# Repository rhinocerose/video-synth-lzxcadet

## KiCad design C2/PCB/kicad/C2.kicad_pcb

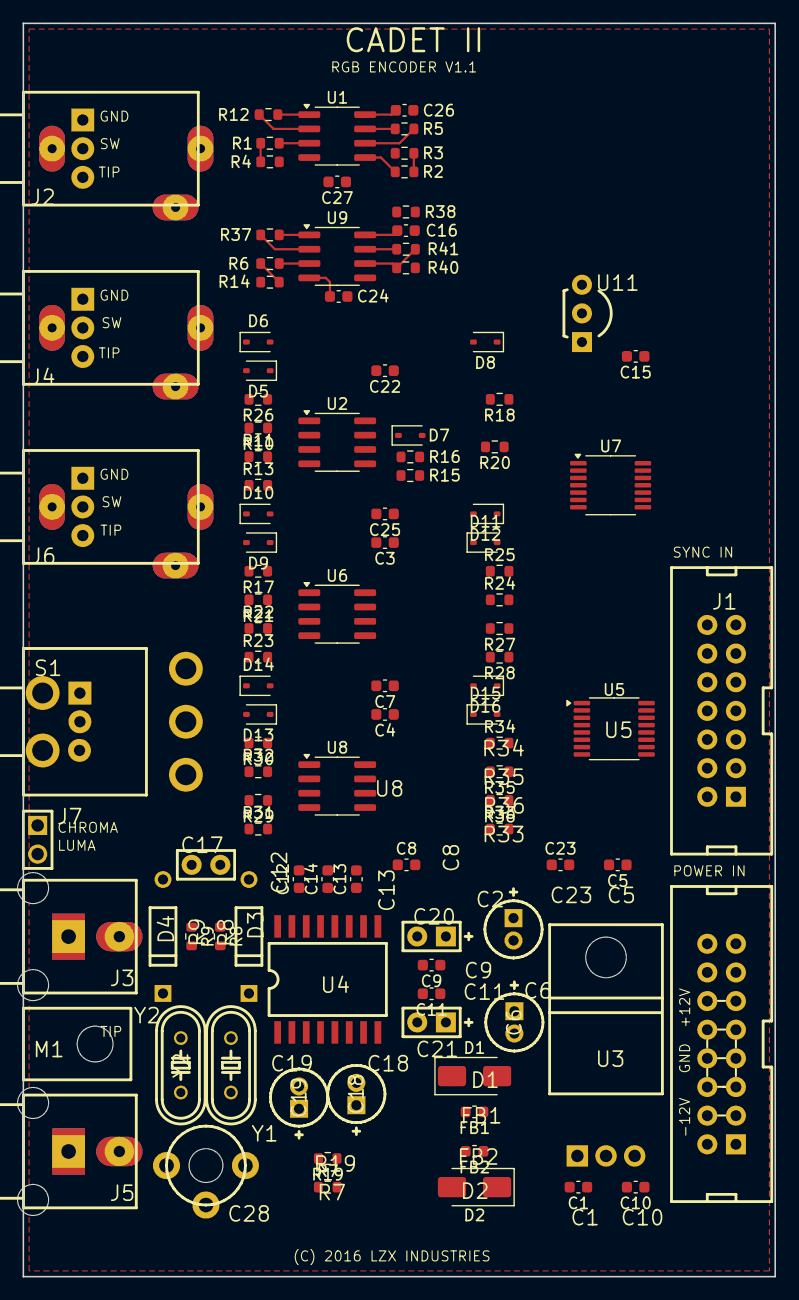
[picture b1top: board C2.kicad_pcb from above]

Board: 2 copper layers, 66.7 x 111.1 mm, 108 parts (0 on the bottom side), 77 nets.

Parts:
C1: 330n; C_0603_1608Metric
C2, C6: 10u 25V; CAPPR-2_5.08
C3, C4, C5, C7, C8, C10, C12, C13, C14, C15, C16, C22, C23, C24, C25, C26, C27: 100n; C_0603_1608Metric
C9, C11: 1u; C_0603_1608Metric
C17: DNP; CAP-2.54_6.6x3_C17
C18, C19: 220uF 6.3V; CAPPR-2_5.08
C20: 10u Tantalum; PCAP-2.54_6.6x3
C21: 10u Tantalum; PCAP-2.54_6.6x3_C21
C28: DNP; GYA22000
D1, D2: 1N4001; D_SMA
D3, D4: 1N4148; DO-35
D5, D6, D7, D8, D9, D10, D11, D12, D13, D14, D15, D16: 1N5711; D_SOD-323
FB1, FB2: 68R; L_0603_1608Metric
J1: LZXSYNC14; IDC14M
J2, J4, J6: 3.5MM_JACK; PJ302M
J3, J5: RCJ-04X
J7: 1X2 PIN HEADER; HDR-2x1T_2.54x2.54_3x5
J9: 2X8_PIN_HEADER; IDC16M
M1: KEYSTONE621
R1, R2, R6: 499R; R_0603_1608Metric
R3, R4, R14: 100K; R_0603_1608Metric
R5, R10, R11, R12, R15, R16, R17, R18, R20, R21, R22, R24, R25, R26, R27, R28, R29, R30, R31, R33, R34, R35, R36, R37, R41: 1K; R_0603_1608Metric
R7, R19: 75R; R_0603_1608Metric
R8, R9: 10K; R_0603_1608Metric
R13, R23, R32: 1.4K; R_0603_1608Metric
R38: 4.99K; R_0603_1608Metric
R40: 3.48K; R_0603_1608Metric
S1: 10TF230-DIY
U1, U2, U6, U8, U9: LM6172; SOIC-8_3.9x4.9mm_P1.27mm
U3: 7805; TO-220H
U4: AD724; SOIC-16_300mil
U5: CD4053; TSSOP-16_4.4x5mm_P0.65mm
U7: 74HC14; TSSOP-14_4.4x5mm_P0.65mm
U11: TL431; TO-92-100R
Y1: 3.58MHz; HC-49U
Y2: 4.43MHz; HC-49U

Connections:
+5V: C5.1, C9.1, C10.1, C11.1, C15.1, C20.1, C21.1, S1.3 (C2), S1.3B (C2), U3.3 (OUTPUT), U4.4, U4.5, U4.14, U4.15, U5.16 (VCC), U7.14 (VCC)
+12V: C1.1, C2.1 (PLUS), C3.1, C4.1, C16.1, C22.1, C26.1, FB1.2, R38.2 (B), U1.8 (V+), U3.1 (INPUT), U6.8 (V+), U8.8 (V+), U9.8 (V+)
-12V: C6.2 (MINUS), C7.2, C8.2, C23.2, C24.2, C25.2, C27.2, FB2.2, U1.4 (V-), U2.4 (V-), U5.7 (VEE), U6.4 (V-), U8.4 (V-), U9.4 (V-)
/Schematic1/2/CLIP_REF: R11.1 (A), R18.1 (A), R22.1 (A), R27.1 (A), R31.1 (A), R35.1 (A), R41.2 (B), U9.7 (OUT)
/Schematic2/2/BLANKING: U5.9 (C), U5.10 (B), U5.11 (A), U7.4 (Y)
BLUE_BLANKING: D16.1 (K), R34.2 (B), U5.3 (Z1)
GND: C1.2, C3.2, C4.2, C5.2, C7.1, C8.1, C9.2, C10.2, C11.2, C15.2, C16.2, C22.2, C23.1, C24.1, C25.1, C26.2, C27.1, C28.CW, D3.1 (K), D4.1 (K), J1.1 (GND), J1.2 (GND), J3.1 (Sleeve), J5.1 (Sleeve), S1.1 (C3), S1.1B (C3), U2.3 (IN+), U2.5 (IN+), U3.2 (GND), U5.2 (Y0), U5.5 (Z0), U5.6 (~EN), U5.8 (GND), U5.12 (X0), U6.3 (IN+), U6.5 (IN+), U7.7 (GND), U7.13 (A), U8.3 (IN+), U8.5 (IN+), U9.5 (IN+), U11.2 (A)
GREEN_BLANKING: D12.1 (K), R25.2 (B), U5.1 (Y1)
unnamed: C2.2 (MINUS), C6.1 (PLUS), J9.3 (GND), J9.4 (GND), J9.5 (GND)
unnamed: D1.2 (A), J9.9 (+12V), J9.10 (+12V)
unnamed: D1.1 (K), FB1.1
unnamed: D2.2 (A), FB2.1
unnamed: D2.1 (K), J9.1 (-12V), J9.2 (-12V)
unnamed: D3.2 (A), R8.1 (A), Y1.1 (OSC1)
unnamed: D4.2 (A), R9.1 (A), Y2.1 (OSC1)
unnamed: D5.2 (A), R10.2 (B)
unnamed: D5.1 (K), D6.2 (A), U2.1 (OUT)
unnamed: D6.1 (K), R20.1 (A), R26.2 (B)
unnamed: D7.2 (A), R15.2 (B)
unnamed: D7.1 (K), D8.2 (A), U2.7 (OUT)
unnamed: D9.2 (A), R17.2 (B)
unnamed: D9.1 (K), D10.2 (A), U6.1 (OUT)
unnamed: D10.1 (K), R21.2 (B), R28.1 (A)
unnamed: D11.2 (A), R24.2 (B)
unnamed: D11.1 (K), D12.2 (A), U6.7 (OUT)
unnamed: D13.2 (A), R29.2 (B)
unnamed: D13.1 (K), D14.2 (A), U8.1 (OUT)
unnamed: D14.1 (K), R30.2 (B), R36.1 (A)
unnamed: D15.2 (A), R33.2 (B)
unnamed: D15.1 (K), D16.2 (A), U8.7 (OUT)
unnamed: J1.7 (Burst_Gate), J1.8 (Burst_Gate)
unnamed: J1.11 (H_Sync), J1.12 (H_Sync)
unnamed: J1.5 (Odd/Even), J1.6 (Odd/Even)
unnamed: J1.9 (V_Sync), J1.10 (V_Sync)
unnamed: J2.2A (Switch), J2.2B (Switch)
unnamed: J3.2 (Tip), R7.2 (B)
unnamed: J4.2A (Switch), J4.2B (Switch)
unnamed: J5.2 (Tip), R19.2 (B)
unnamed: J6.2A (Switch), J6.2B (Switch)
unnamed: J9.11 (+5V), J9.12 (+5V)
unnamed: J9.13 (CV), J9.14 (CV)
unnamed: J9.15 (Gate), J9.16 (Gate)
unnamed: J2.3A (Tip), J2.3B (Tip), R1.1 (A), R4.2 (B)
unnamed: R1.2 (B), U1.3 (IN+)
unnamed: J4.3A (Tip), J4.3B (Tip), R2.1 (A), R3.2 (B)
unnamed: R2.2 (B), U1.5 (IN+)
unnamed: R5.1 (A), U1.6 (IN-)
unnamed: R6.2 (B), U9.3 (IN+)
unnamed: R8.2 (B), S1.2 (C1), S1.2B (C1), U7.11 (A)
unnamed: R9.2 (B), U7.10 (Y)
unnamed: R10.1 (A), R11.2 (B), R13.2 (B), R26.1 (A), U2.2 (IN-)
unnamed: R12.1 (A), U1.2 (IN-)
unnamed: R12.2 (B), R13.1 (A), U1.1 (OUT)
unnamed: J6.3A (Tip), J6.3B (Tip), R6.1 (A), R14.2 (B)
unnamed: R15.1 (A), R16.1 (A), R18.2 (B), R20.2 (B), U2.6 (IN-)
unnamed: R17.1 (A), R21.1 (A), R22.2 (B), R23.2 (B), U6.2 (IN-)
unnamed: R5.2 (B), R23.1 (A), U1.7 (OUT)
unnamed: R24.1 (A), R25.1 (A), R27.2 (B), R28.2 (B), U6.6 (IN-)
unnamed: R29.1 (A), R30.1 (A), R31.2 (B), R32.2 (B), U8.2 (IN-)
unnamed: R32.1 (A), R37.2 (B), U9.1 (OUT)
unnamed: R33.1 (A), R34.1 (A), R35.2 (B), R36.2 (B), U8.6 (IN-)
unnamed: R37.1 (A), U9.2 (IN-)
unnamed: R38.1 (A), R40.1 (A), U11.1 (K), U11.3 (REF)
unnamed: R40.2 (B), R41.1 (A), U9.6 (IN-)
unnamed: C28.CCW, C28.W, Y1.2 (OSC2), Y2.2 (OSC2)
unnamed: C13.1, U5.14 (X)
unnamed: C12.1, U5.15 (Y)
unnamed: C14.1, U5.4 (Z)
unnamed: J1.3 (Blanking), J1.4 (Blanking), U7.1 (A)
unnamed: U7.2 (Y), U7.3 (A)
unnamed: J1.13 (C_Sync), J1.14 (C_Sync), U7.5 (A)
unnamed: U7.6 (Y), U7.9 (A)
Net_38: C17.1, U4.3
Net_53: C17.2, C20.2, C21.2, J2.1A (Sleeve), J2.1B (Sleeve), J4.1A (Sleeve), J4.1B (Sleeve), J6.1A (Sleeve), J6.1B (Sleeve), R3.1 (A), R4.1 (A), R14.1 (A), U4.2, U4.12, U4.13
Net_70: J7.1, U4.9
Net_71: J7.2, U4.11
RED_BLANKING: D8.1 (K), R16.2 (B), U5.13 (X1)

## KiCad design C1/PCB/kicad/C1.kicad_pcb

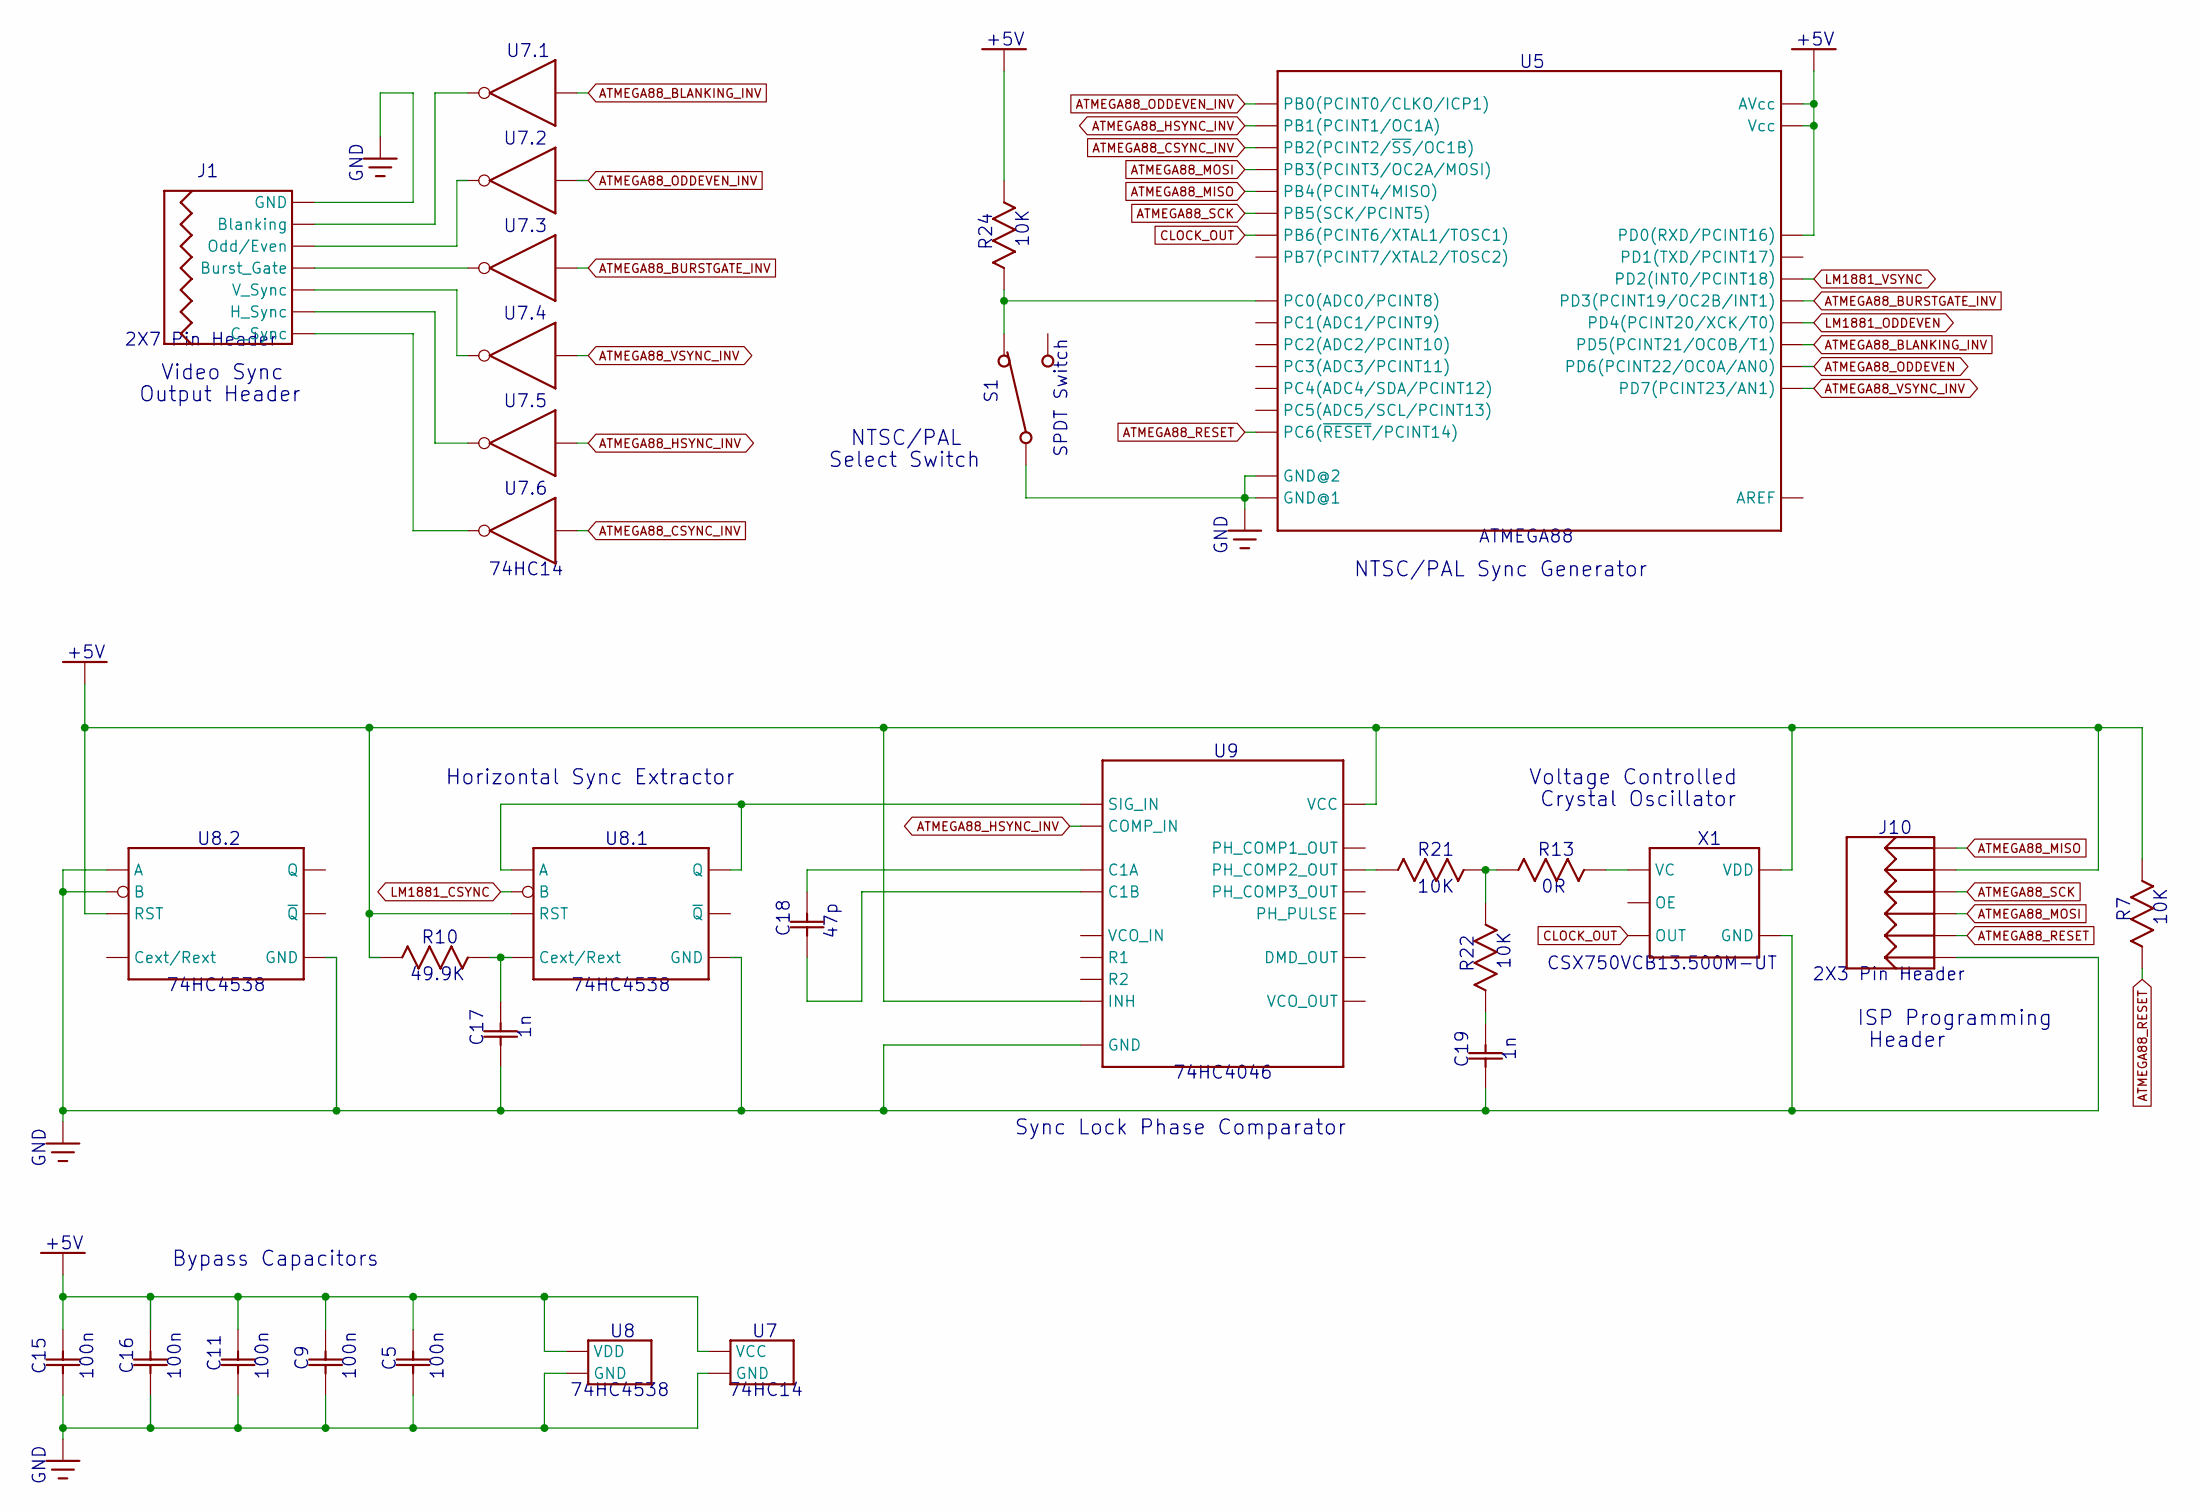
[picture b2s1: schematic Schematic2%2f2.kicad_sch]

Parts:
C5, C9, C11, C15, C16: 100n; C_0603_1608Metric
C17, C19: 1n; C_0603_1608Metric
C18: 47p; C_0603_1608Metric
J1: 2X7_PIN_HEADER; IDC14M
J10: 2X3_PIN_HEADER; HDR-2X3T_2.54X2.54_8X5
R7, R21, R22, R24: 10K; R_0603_1608Metric
R10: 49.9K; R_0603_1608Metric
R13: 0R; R_0603_1608Metric
S1: SPDT_SWITCH; 10TF230-DIY
U5: ATMEGA88; TQFP-32_7x7mm_P0.8mm
U7: 74HC14; TSSOP-14_4.4x5mm_P0.65mm
U8: 74HC4538; TSSOP-16_4.4x5mm_P0.65mm
U9: 74HC4046; TSSOP-16_4.4x5mm_P0.65mm
X1: CSX750VCB13.500M-UT; CSX-750V

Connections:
+5V: C5.1, C9.1, C11.1, C15.1, C16.1, J10.2, R7.2 (B), R10.2 (B), R24.1 (A), U5.2 (PD0(RXD/PCINT16)), U5.7 (Vcc), U5.20 (AVcc), U7.14 (VCC), U8.3 (RST), U8.13 (RST), U8.16 (VDD), U9.5 (INH), U9.16 (VCC), X1.6 (VDD); also elsewhere on the board
ATMEGA88_BLANKING_INV: U5.11 (PD5(PCINT21/OC0B/T1)), U7.1 (A)
ATMEGA88_BURSTGATE_INV: U5.5 (PD3(PCINT19/OC2B/INT1)), U7.5 (A)
ATMEGA88_CSYNC_INV: U5.16 (PB2(PCINT2/~SS/OC1B)), U7.13 (A)
ATMEGA88_HSYNC_INV: U5.15 (PB1(PCINT1/OC1A)), U7.11 (A), U9.3 (COMP_IN); also elsewhere on the board
ATMEGA88_MISO: J10.1, U5.18 (PB4(PCINT4/MISO))
ATMEGA88_MOSI: J10.4, U5.17 (PB3(PCINT3/OC2A/MOSI))
ATMEGA88_ODDEVEN: U5.12 (PD6(PCINT22/OC0A/AN0)); also elsewhere on the board
ATMEGA88_ODDEVEN_INV: U5.14 (PB0(PCINT0/CLKO/ICP1)), U7.3 (A)
ATMEGA88_RESET: J10.5, R7.1 (A), U5.1 (PC6(~RESET/PCINT14))
ATMEGA88_SCK: J10.3, U5.19 (PB5(SCK/PCINT5))
ATMEGA88_VSYNC_INV: U5.13 (PD7(PCINT23/AN1)), U7.9 (A); also elsewhere on the board
CLOCK_OUT: U5.9 (PB6(PCINT6/XTAL1/TOSC1)), X1.4 (OUT)
LM1881_CSYNC: U8.5 (B); also elsewhere on the board
LM1881_ODDEVEN: U5.6 (PD4(PCINT20/XCK/T0)); also elsewhere on the board
LM1881_VSYNC: U5.4 (PD2(INT0/PCINT18)); also elsewhere on the board
unnamed: C17.1, R10.1 (A), U8.2 (Cext/Rext)
unnamed: R13.1 (A), X1.1 (VC)
unnamed: R13.2 (B), R21.2 (B), R22.1 (A)
unnamed: R21.1 (A), U9.13 (PH_COMP2_OUT)
unnamed: C19.1, R22.2 (B)
unnamed: R24.2 (B), S1.1 (C3), S1.1B (C3), U5.23 (PC0(ADC0/PCINT8))
unnamed: S1.3 (C2), S1.3B (C2)
unnamed: J1.3 (Blanking), J1.4 (Blanking), U7.2 (Y)
unnamed: J1.5 (Odd/Even), J1.6 (Odd/Even), U7.4 (Y)
unnamed: J1.7 (Burst_Gate), J1.8 (Burst_Gate), U7.6 (Y)
unnamed: J1.9 (V_Sync), J1.10 (V_Sync), U7.8 (Y)
unnamed: J1.11 (H_Sync), J1.12 (H_Sync), U7.10 (Y)
unnamed: J1.13 (C_Sync), J1.14 (C_Sync), U7.12 (Y)
unnamed: U8.4 (A), U8.6 (Q), U9.14 (SIG_IN)
unnamed: C18.1, U9.6 (C1A)
unnamed: C18.2, U9.7 (C1B)

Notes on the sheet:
74HC4538
2X7 Pin Header
2X3 Pin Header
Header
Crystal Oscillator
Horizontal Sync Extractor
C18
U7.4
100n
U7.5
+5V
C15
SPDT Switch
NTSC/PAL
Sync Lock Phase Comparator
74HC14
Video Sync
10K
C19
Select Switch
GND
U7.3
R24
C17
Output Header
ATMEGA88
U7.2
U7.6
R22
74HC4046
U7.1
C11
CSX750VCB13.500M-UT
47p
J10
Bypass Capacitors
R13
Voltage Controlled
U8.2
C16

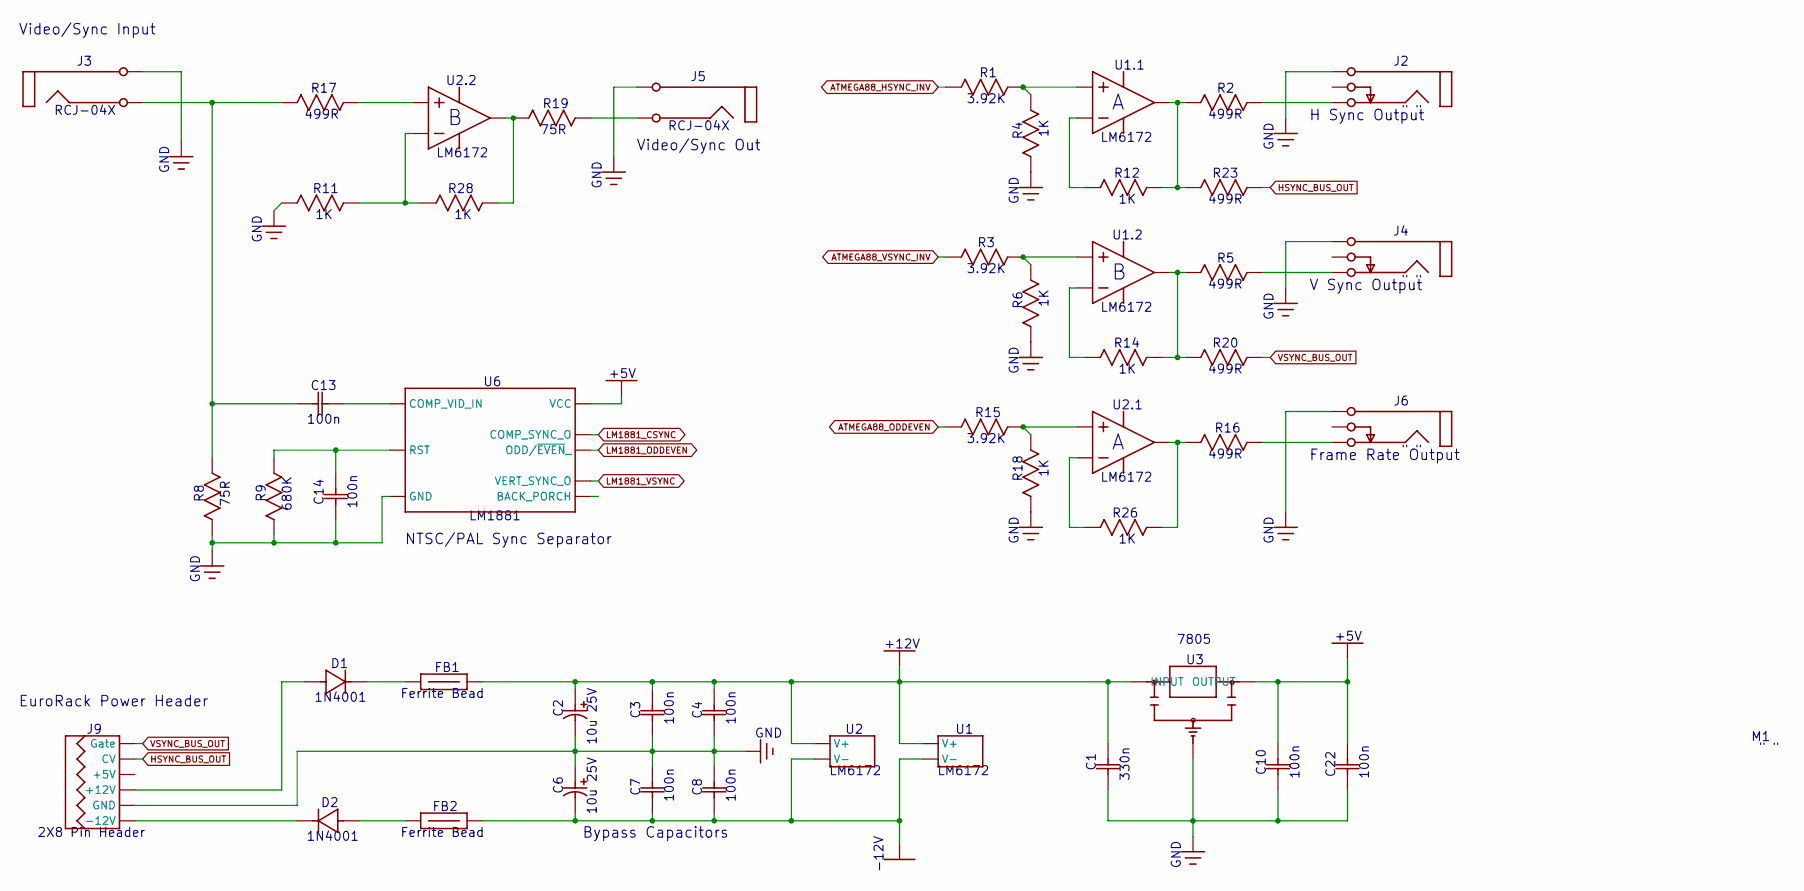
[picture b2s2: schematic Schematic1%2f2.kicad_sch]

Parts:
C1: 330n; C_0603_1608Metric
C2, C6: 10u 25V; CAPPR-2_5.08
C3, C4, C7, C8, C10, C13, C14, C22: 100n; C_0603_1608Metric
D1, D2: 1N4001; D_SMA
FB1, FB2: 68R; L_0603_1608Metric
J2, J4, J6: 3.5MM_JACK; PJ302M
J3: RCJ-04X
J5: RCJ-04X_23; RCJ-04X
J9: 2X8_PIN_HEADER; IDC16M
M1: KEYSTONE621
R1, R3, R15: 3.92K; R_0603_1608Metric
R2, R5, R16, R17, R20, R23: 499R; R_0603_1608Metric
R4, R6, R11, R12, R14, R18, R26, R28: 1K; R_0603_1608Metric
R8, R19: 75R; R_0603_1608Metric
R9: 680K; R_0603_1608Metric
U1, U2: LM6172; SOIC-8_3.9x4.9mm_P1.27mm
U3: 7805; TO-220H
U6: LM1881; SOIC-8_3.9x4.9mm_P1.27mm

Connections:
+5V: C10.1, C22.1, U3.3 (OUTPUT), U6.8 (VCC); also elsewhere on the board
+12V: C1.1, C2.1 (PLUS), C3.1, C4.1, FB1.2, U1.8 (V+), U2.8 (V+), U3.1 (INPUT)
-12V: C6.2 (MINUS), C7.2, C8.2, FB2.2, U1.4 (V-), U2.4 (V-)
ATMEGA88_HSYNC_INV: R1.1 (A); also elsewhere on the board
ATMEGA88_ODDEVEN: R15.1 (A); also elsewhere on the board
ATMEGA88_VSYNC_INV: R3.1 (A); also elsewhere on the board
HSYNC_BUS_OUT: J9.13 (CV), J9.14 (CV), R23.2 (B)
LM1881_CSYNC: U6.1 (COMP_SYNC_O); also elsewhere on the board
LM1881_ODDEVEN: U6.7 (ODD/~EVEN_); also elsewhere on the board
LM1881_VSYNC: U6.3 (VERT_SYNC_O); also elsewhere on the board
unnamed: D1.2 (A), J9.9 (+12V), J9.10 (+12V)
unnamed: D1.1 (K), FB1.1
unnamed: D2.2 (A), FB2.1
unnamed: D2.1 (K), J9.1 (-12V), J9.2 (-12V)
unnamed: J2.2A (Switch), J2.2B (Switch)
unnamed: C13.1, J3.2 (Tip), R8.2 (B), R17.1 (A)
unnamed: J4.2A (Switch), J4.2B (Switch)
unnamed: J5.2 (Tip), R19.2 (B)
unnamed: J6.2A (Switch), J6.2B (Switch)
unnamed: J9.11 (+5V), J9.12 (+5V)
unnamed: R1.2 (B), R4.2 (B), U1.3 (IN+)
unnamed: J2.3A (Tip), J2.3B (Tip), R2.2 (B)
unnamed: R3.2 (B), R6.2 (B), U1.5 (IN+)
unnamed: J4.3A (Tip), J4.3B (Tip), R5.2 (B)
unnamed: C14.2, R9.2 (B), U6.6 (RST)
unnamed: R11.2 (B), R28.1 (A), U2.6 (IN-)
unnamed: R12.1 (A), U1.2 (IN-)
unnamed: R2.1 (A), R12.2 (B), R23.1 (A), U1.1 (OUT)
unnamed: R14.1 (A), U1.6 (IN-)
unnamed: R5.1 (A), R14.2 (B), R20.1 (A), U1.7 (OUT)
unnamed: R15.2 (B), R18.2 (B), U2.3 (IN+)
unnamed: R16.1 (A), R26.2 (B), U2.1 (OUT)
unnamed: J6.3A (Tip), J6.3B (Tip), R16.2 (B)
unnamed: R17.2 (B), U2.5 (IN+)
unnamed: R19.1 (A), R28.2 (B), U2.7 (OUT)
unnamed: R26.1 (A), U2.2 (IN-)
unnamed: C13.2, U6.2 (COMP_VID_IN)
VSYNC_BUS_OUT: J9.15 (Gate), J9.16 (Gate), R20.2 (B)

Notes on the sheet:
100n
U2.1
LM6172
GND
C10
V Sync Output
NTSC/PAL Sync Separator
" "
FB2
RCJ-04X
C13
Ferrite Bead
499R
EuroRack Power Header
75R
U2.2
-12V
3.92K
Video/Sync Input
R28
R15
R12
2X8 Pin Header
U1.2
C22
7805
+5V
C14
10u 25V
R19
R26
330n
R17
+12V
680K
1N4001
U1.1
Frame Rate Output
R20
R14

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
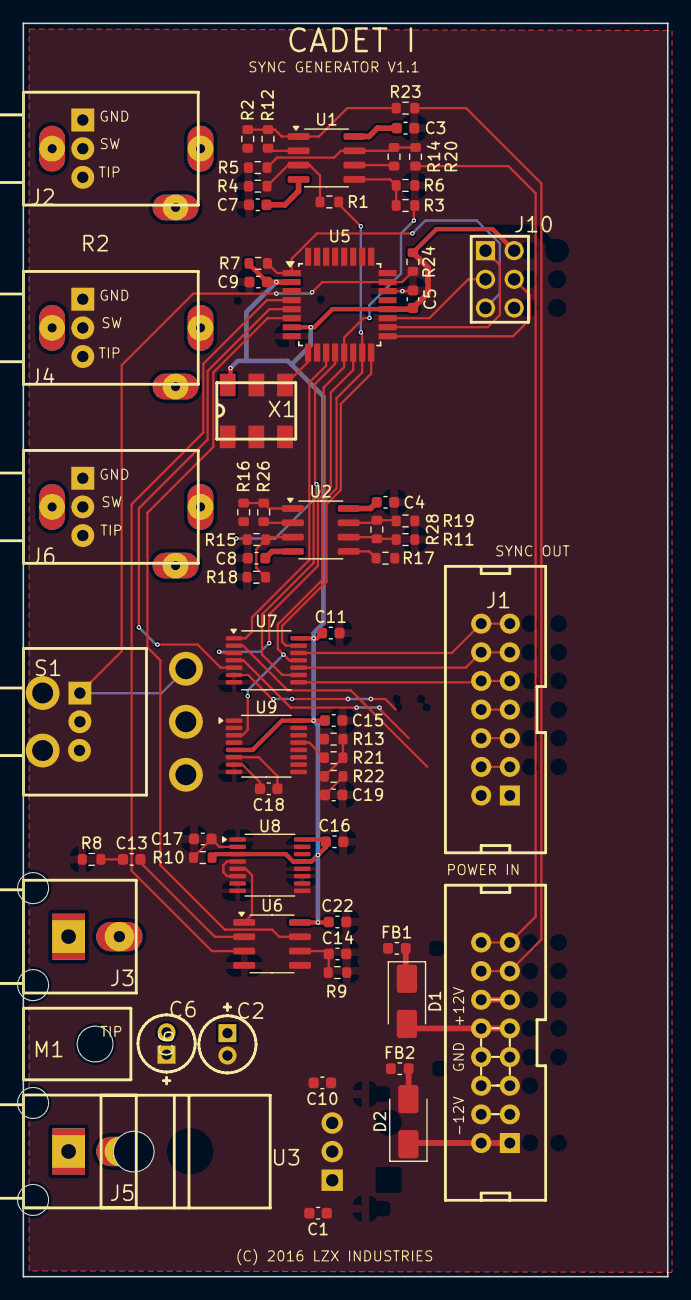
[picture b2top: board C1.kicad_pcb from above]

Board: 2 copper layers, 57.1 x 111.1 mm, 68 parts (0 on the bottom side), 64 nets.

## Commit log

2025-08-17 Started converting to Eagle
2025-08-18 Done through C5
2025-08-18 All converted to Eagle
2025-08-25 Started work on C2

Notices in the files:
C1/PCB/kicad/C1.kicad_pcb:
(C) 2016 LZX INDUSTRIES
